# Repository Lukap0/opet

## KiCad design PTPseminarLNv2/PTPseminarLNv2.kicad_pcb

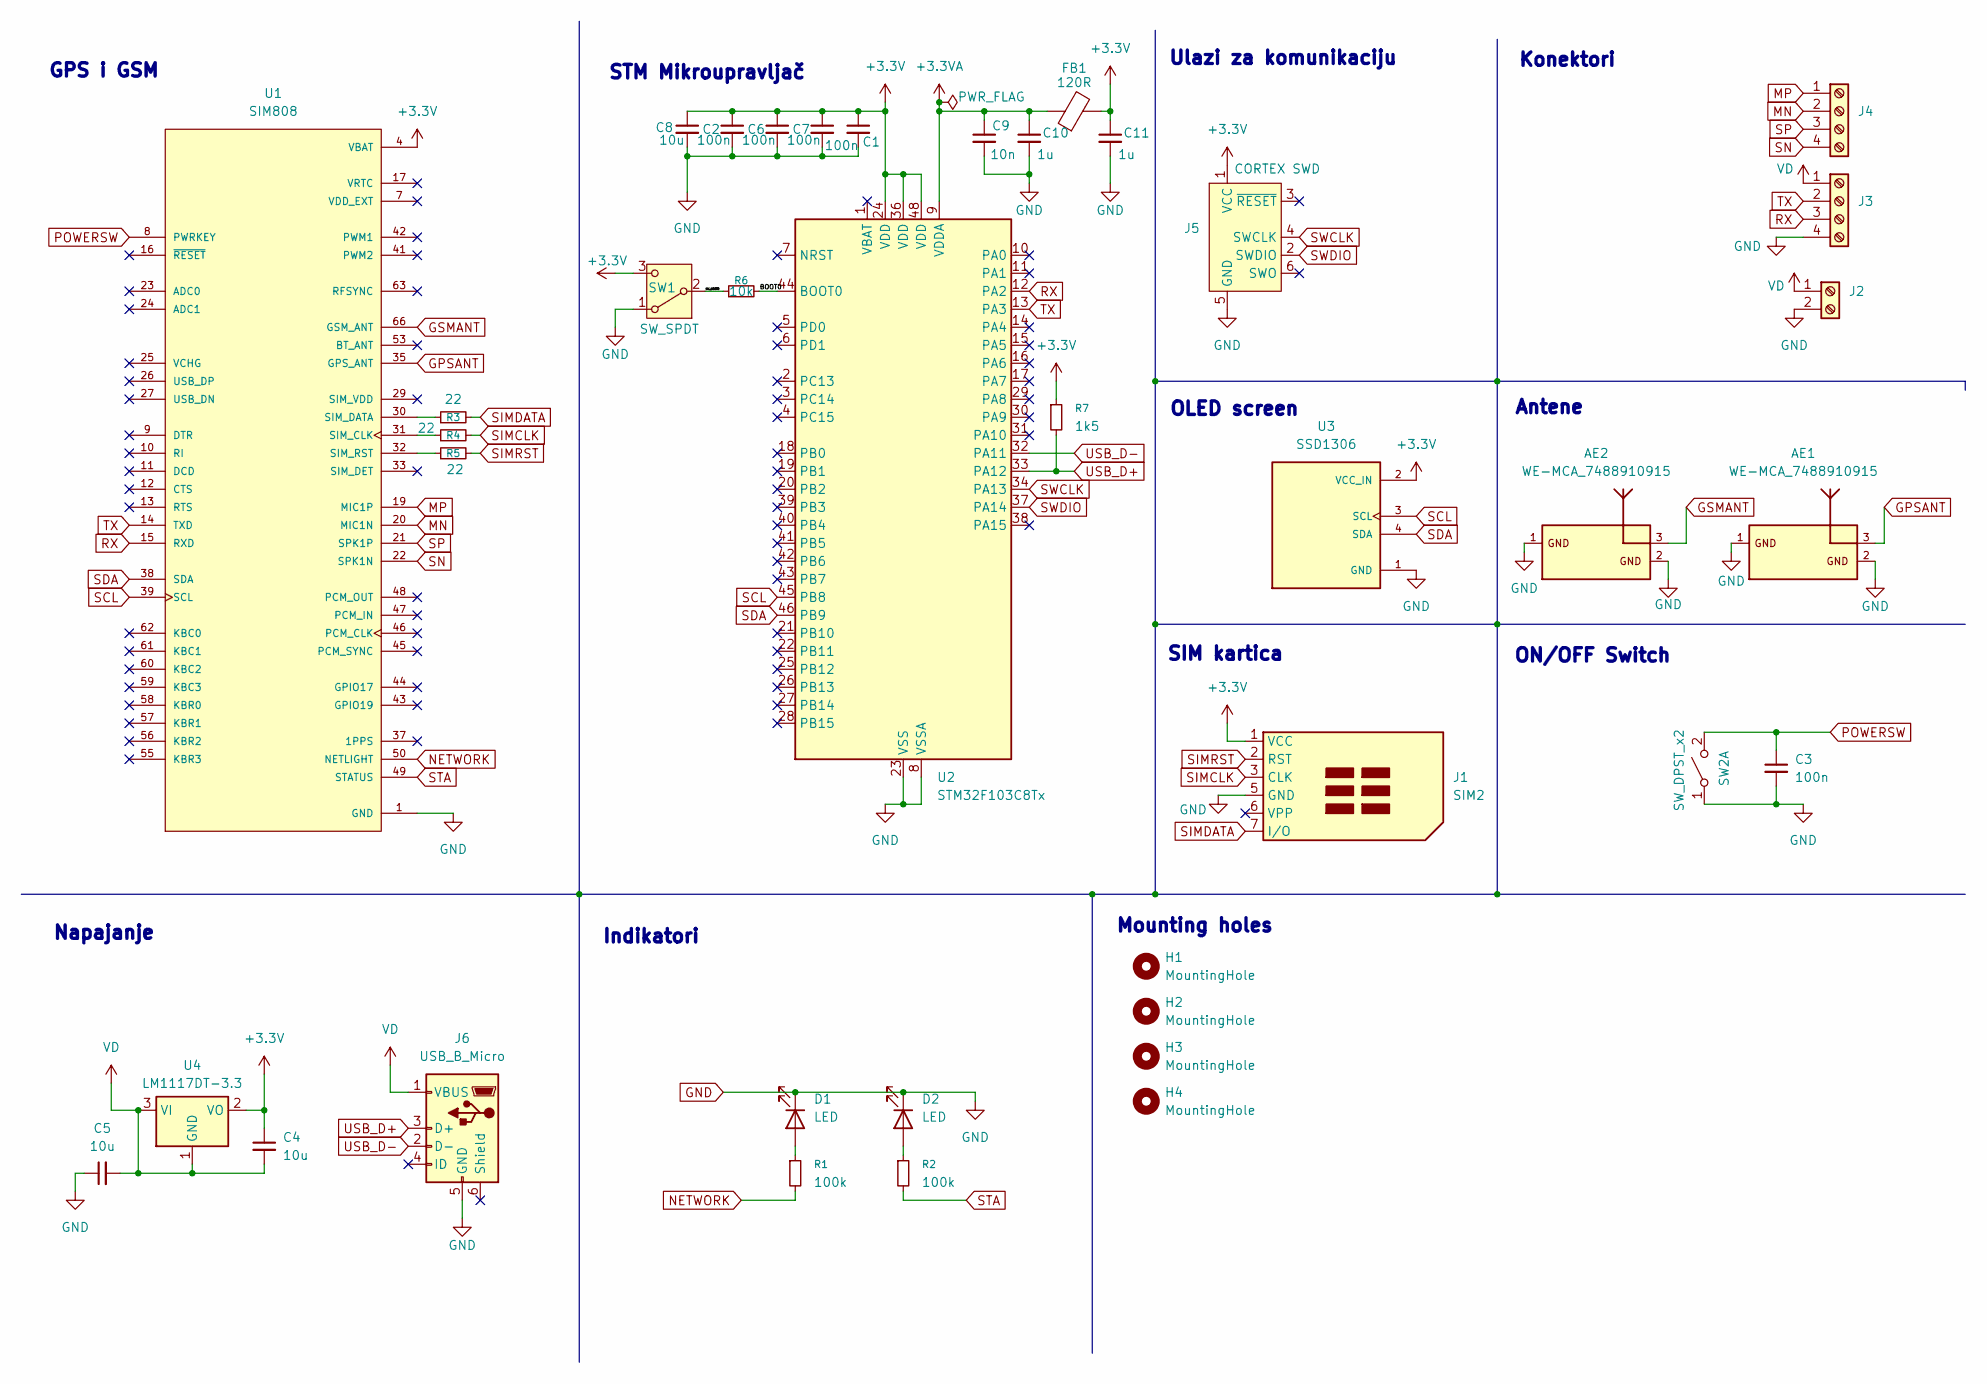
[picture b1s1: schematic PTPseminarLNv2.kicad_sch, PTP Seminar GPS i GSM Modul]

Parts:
AE1, AE2: WE-MCA_7488910915; Manufacturer part number 7488910915
C1, C3, C6, C7: 100n; C_1206_3216Metric_Pad1.33x1.80mm_HandSolder; Manufacturer part number GRM31CR71H104KA88L
C2: 100n; C_1206_3216Metric_Pad1.33x1.80mm_HandSolder; Manufactuer part number GRM31CR71H104KA88L
C4, C5, C8: 10u; C_1206_3216Metric_Pad1.33x1.80mm_HandSolder; Manufacturer part number GRM31CR61C106KA12L
C9: 10n; C_1206_3216Metric_Pad1.33x1.80mm_HandSolder; Manufacturer part number GRM31CR71H103KA01L
C10, C11: 1u; C_1206_3216Metric_Pad1.33x1.80mm_HandSolder; Manufacturer part number GRM31CR61C106KA12L
D1, D2: LED; LED_1206_3216Metric_Pad1.42x1.75mm_HandSolder; Manufacturer part number LTST-C191KRKT
FB1: 120R; LairdTech_28C0236-0JW-10; Manufacturer part number BLM31AG121SN1L
H1, H2, H3, H4: MountingHole; MountingHole_6mm
J1: SIM2; TE_2452808-1; Manufacturer part number 2452808-1
J2: PinHeader_1x02_P2.00mm_Vertical; Manufacturer part number B2B-XH-A
J3, J4: FanPinHeader_1x04_P2.54mm_Vertical; Manufacturer part number B4B-PH-K-S
J5: CORTEX SWD; ARM-JTAG-10-SWD-IDC; Manufacturer part number TC2030-CTX
J6: USB_B_Micro; USB_Mini-B_Lumberg_2486_01_Horizontal; Manufacturer part number 2486 01
R1, R2: 100k; R_1206_3216Metric_Pad1.30x1.75mm_HandSolder; Manufacturer part number RC1206JR-07100KL
R3, R4, R5: 22; R_1206_3216Metric_Pad1.30x1.75mm_HandSolder; Manufacturer part number RC1206JR-0722RL
R6: 10k; R_1206_3216Metric_Pad1.30x1.75mm_HandSolder; Manufacturer part number RC1206JR-0710KL
R7: 1k5; R_1206_3216Metric_Pad1.30x1.75mm_HandSolder; Manufacturer part number RC1206JR-071K5L
SW1: SW_SPDT; SW_Slide_SPDT_Straight_CK_OS102011MS2Q; Manufacturer part number OS102011MS2Q
SW2: SW_DPST_x2; SW_DIP_SPSTx01_Slide_Omron_A6S-110x_W8.9mm_P2.54mm; Manufacturer part number A6S-1101
U1: SIM808; XCVR_SIM808; Manufacturer part number XCVR_SIM808
U2: STM32F103C8Tx; LQFP-48_7x7mm_P0.5mm; Manufacturer part number STM32F103C8Tx
U3: SSD1306; MODULE_DM-OLED096-636; Manufacturer part number DM-OLED096-636
U4: LM1117DT-3.3; TO-252-3_TabPin2; Manufacturer part number LM1117DT-3.3/NOPB

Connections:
+3.3V: C1.1, C2.1, C4.1, C6.1, C7.1, C8.1, C11.1, FB1.2, J1.1 (VCC), J5.1 (VCC), R7.1, SW1.3 (C), U1.4 (VBAT), U2.24 (VDD), U2.36 (VDD), U2.48 (VDD), U3.2 (VCC_IN), U4.2 (VO)
+3.3VA: C9.1, C10.1, FB1.1, U2.9 (VDDA)
/BOOT0: R6.2, U2.44 (BOOT0)
/SW_BOOT0: R6.1, SW1.2 (B)
GND: AE1.1, AE1.2, AE2.1, AE2.2, C1.2, C2.2, C3.2, C5.1, C6.2, C7.2, C8.2, C9.2, C10.2, C11.2, D1.1 (K), D2.1 (K), J1.5 (GND), J2.2, J3.4, J5.5 (GND), J6.5 (GND), SW1.1 (A), SW2.1 (A), U1.1 (GND), U1.2 (GND), U1.3 (GND), U1.18 (GND), U1.28 (GND), U1.34 (GND), U1.36 (GND), U1.40 (GND), U1.51 (GND), U1.52 (GND), U1.54 (GND), U1.64 (GND), U1.65 (GND), U1.67 (GND), U1.68 (GND), U2.8 (VSSA), U2.23 (VSS), U2.35 (VSS), U2.47 (VSS), U3.1 (GND)
GPSANT: AE1.3, U1.35 (GPS_ANT)
GSMANT: AE2.3, U1.66 (GSM_ANT)
MN: J4.2, U1.20 (MIC1N)
MP: J4.1, U1.19 (MIC1P)
NETWORK: R1.2, U1.50 (NETLIGHT)
unnamed: D1.2 (A), R1.1
unnamed: D2.2 (A), R2.1
unnamed: R4.1, U1.31 (SIM_CLK)
unnamed: R3.1, U1.30 (SIM_DATA)
unnamed: R5.1, U1.32 (SIM_RST)
POWERSW: C3.1, SW2.2 (B), U1.8 (PWRKEY)
RX: J3.3, U1.15 (RXD), U2.12 (PA2)
SCL: U1.39 (SCL), U2.45 (PB8), U3.3 (SCL)
SDA: U1.38 (SDA), U2.46 (PB9), U3.4 (SDA)
SIMCLK: J1.3 (CLK), R4.2
SIMDATA: J1.7 (I/O), R3.2
SIMRST: J1.2 (RST), R5.2
SN: J4.4, U1.22 (SPK1N)
SP: J4.3, U1.21 (SPK1P)
STA: R2.2, U1.49 (STATUS)
SWCLK: J5.4 (SWCLK), U2.34 (PA13)
SWDIO: J5.2 (SWDIO), U2.37 (PA14)
TX: J3.2, U1.14 (TXD), U2.13 (PA3)
USB_D+: J6.3 (D+), R7.2, U2.33 (PA12)
USB_D-: J6.2 (D-), U2.32 (PA11)
VD: C4.2, C5.2, J2.1, J3.1, J6.1 (VBUS), U4.1 (GND), U4.3 (VI)

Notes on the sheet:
SIM kartica
Napajanje
Indikatori
ON/OFF Switch
Konektori
Mounting holes
OLED screen
Antene
STM Mikroupravljač
GPS i GSM
Ulazi za komunikaciju

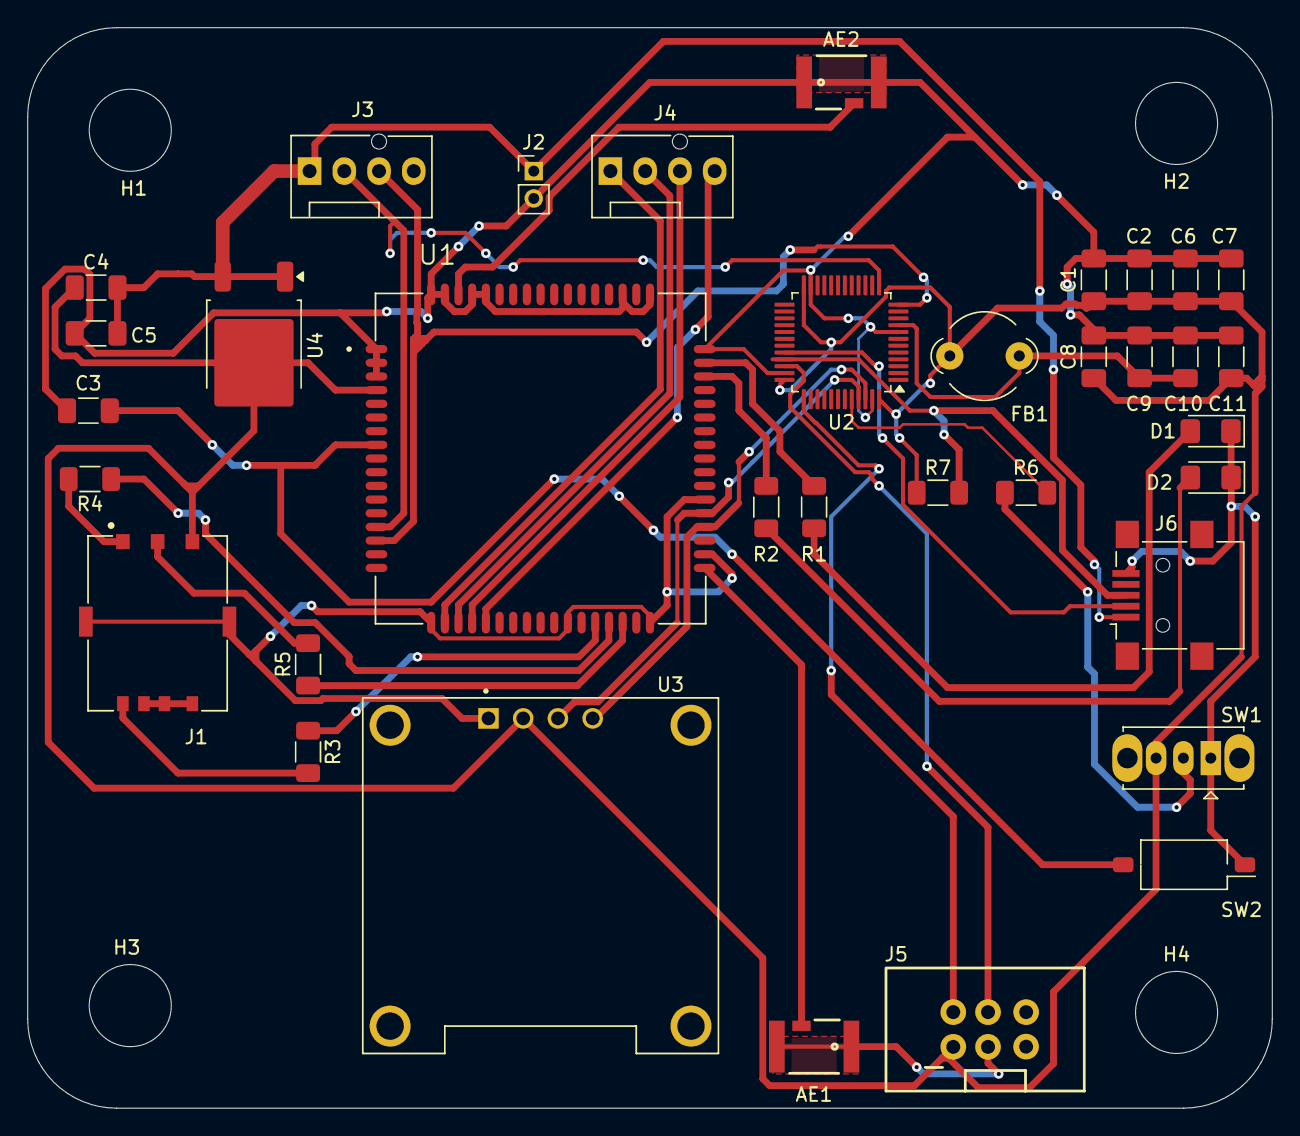
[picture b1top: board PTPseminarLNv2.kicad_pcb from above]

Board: 2 copper layers, 91.0 x 79.0 mm, 39 parts (0 on the bottom side), 31 nets.

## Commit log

2026-01-22 totiturumtututu
    tutu
2026-01-22 3dmod
2026-01-22 bato
    naanajjace
2026-01-26 skoro gotovi
    na najjace
2026-01-26 uf
    oke
2026-01-27 finito
    fin
